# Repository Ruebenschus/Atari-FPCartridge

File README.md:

Atari-FPCartridge
=================

**Atari Field Programmable Cartridge**

Use an ULX3S FPGA to emulate an Atari ST cartridge.

Overview
--------

Atari-FPCartridge is a proof-of-concept adapter and FPGA design that connects a
ULX3S board to the Atari ST cartridge port. The goal is to make cartridge
development, boot analysis, ROM emulation, and hardware experimentation much
easier without building a custom FPGA board from scratch on day one.

The project combines:

-   a KiCad adapter PCB for the Atari ST cartridge connector and the ULX3S
    headers

-   level shifting between the 5 V Atari bus and the 3.3 V FPGA I/O

-   power-path selection between Atari 5 V and ULX3S USB 5 V

-   FPGA firmware for cartridge emulation, diagnostics, display output, and
    bus-oriented test modes

The result is a practical development platform for exploring what the Atari ST
expects at the cartridge port and for gradually moving toward more advanced
cartridge behavior.

Why ULX3S + FPGA
----------------

An FPGA is a good fit for this job because the Atari cartridge port is
fundamentally a parallel hardware interface. An FPGA can react
deterministically, observe many signals at once, and eventually emulate ROM
behavior with cycle-level control.

Compared with a Raspberry Pi or similar SBC:

-   **Advantages of the FPGA approach**

    -   deterministic timing

    -   direct parallel I/O handling

    -   much better fit for ROM emulation and bus experiments

    -   easier path toward cycle-precise cartridge behavior

-   **Disadvantages of the FPGA approach**

    -   HDL development is maybe more complex than software on Linux

    -   higher entry barrier for tooling and synthesis. I’m a hardware designer
        by trade, so it is my natural way of doing thing ;-)

    -   FPGAs are less common and potentially higher cost than e.g. RPI

-   **Advantages of an SBC approach**

    -   easier software stack

    -   networking, file systems, and UI are simpler

    -   fast prototyping for higher-level features

-   **Disadvantages of an SBC approach**

    -   GPIO timing is much less deterministic and has to be tweaked by RPI
        GPIOs

    -   parallel bus interfacing is harder

    -   extra hardware is usually needed to make the interface robust

The ULX3S offers a strong middle ground: a real FPGA, a convenient dev board,
USB programming, built-in buttons, LEDs, OLED support, HDMI video, and future
expansion options such as Wi-Fi-assisted workflows.

A note on SidecarTridge
-----------------------

This project is inspired by the excellent
[SidecarTridge](https://sidecartridge.com/) project. SidecarTridge shows how
much can be achieved when modern programmable logic and the Atari ST cartridge
port are combined thoughtfully. Atari-FPCartridge is not trying to diminish that
work. On the contrary, it is a respectful proof of concept built in the same
spirit: use todays hardware to tweak your old retro Atari and have fun as in the
golden days.  

Hardware
--------

### PCB scope

The adapter PCB is designed to sit between the Atari ST cartridge connector and
the ULX3S board. It provides:

-   Atari cartridge connector breakout

-   ULX3S header connections

-   bidirectional level shifters for the data bus

-   shifted input paths for address and control signals

-   power-path selection between USB power and Atari cartridge power

### Power

The board is intended to support powering the setup from either:

-   **ULX3S USB 5 V**

-   **Atari ST cartridge-port 5 V**

The power section is built around automatic source selection so that:

-   when USB power is present, the ULX3S can power itself and the level shifters
    locally

-   when USB power is absent, the adapter can be powered from the Atari
    cartridge port

This avoids a manual source switch in normal use and keeps the adapter much
easier to operate during development and bring-up.

### Signals

#### Unidirectional signals into the FPGA

These lines are treated as bus-observation inputs from the Atari side:

-   `A1..A15`

-   `ROM3#`

-   `ROM4#`

-   `UDS#`

-   `LDS#`

#### Bidirectional signals

These lines are routed through bidirectional level shifters:

-   `D0..D15`

They can be:

-   read by the FPGA during analysis and test modes

-   driven by the FPGA during cartridge emulation

-   driven selectively in debug output tests

#### FPGA-controlled transceiver signals

The level shifters expose separate control to the FPGA for:

-   `DIR4`

-   `OE4`

-   `DIR5`

-   `OE5`

That keeps the hardware flexible and allows different modes to switch between
safe sniffing, drive tests, and cartridge emulation behavior.

Repository structure
--------------------

-   `kicad/` - schematic, PCB, symbols, footprints

-   `stacy-cart-menu/` - FPGA design, constraints, ROM build flow

Operating modes
---------------

The FPGA project includes a menu on the OLED and several operating modes.

### `diag_cart`

This is the default power-up mode. It presents an Atari ST diagnostic cartridge
ROM image at the cartridge port so the machine can boot directly into the
diagnostic cartridge.

### `boot_analyzer`

This mode is intended to analyze the cartridge boot process and show how far the
system gets. It uses the OLED and the front-panel LEDs to indicate progress.

The LEDs are used as a step display:

-   a LED stays on when a step has been reached

-   a LED blinks slowly while the analyzer is waiting

-   a LED blinks quickly when a step times out or fails

This is useful for checking whether the expected cartridge accesses occur during
boot and whether the machine reaches the expected execution sequence.

### `beep`

This mode uses a small custom cartridge program that was created with AI
assistance and then integrated as a dedicated 68000-side test image. It
demonstrates that the FPGA can present a custom cartridge ROM and make the Atari
execute user-provided code.

In practical terms, it is a very small proof that the design can go beyond
passive observation and actively influence software execution through cartridge
ROM emulation. It makes the speaker beep to see whether the CPU is alive before
even accessing RAM or keyboard.

### `cart-debug`

The debug submenu contains low-level hardware test modes for board bring-up and
signal verification.  It is useful for pin verification and confirming that the
board routing matches the expected net mapping.

#### `drive`

This mode selects one signal at a time (selectable by buttons and OLED menu) and
toggles it at a visible rate so it can be checked with a multimeter or scope.
GP19 acts as read input any one can connect one output after another to the
input and see whether it is toggeling.

#### `read`

This mode is the opposite and lets the FPGA read external signal levels and show
them on the OLED. GP19 is enabled as 1Hz toggeling pin such that just with a
single cable on is capable of checking all solder connections and pins of the
board.  

OLED and LED diagnostics
------------------------

The OLED is used as the primary local UI. It shows:

-   the top-level menu

-   the currently selected cartridge mode

-   the current debug mode

-   analyzer state and captured addresses

The LEDs provide a quick visual status summary without needing to read the
display closely. This is especially useful while powering the Atari on, when
watching both the computer and the adapter at the same time.  
  
The Board also has a HDMI output which could be leveraged in future.  

Building and flashing
---------------------

~~~~~~~~~~~~~~~~~~~~~~~~~~~~~~~~~~~~~~~~~~~~~~~~~~~~~~~~~~~~~~~~~~~~~~~~~~~~~~~~
To build and program the FPGA design, the following tools are required:

- [oss-cad-suite](https://github.com/YosysHQ/oss-cad-suite-build) including:
  - `yosys`
  - `nextpnr-ecp5`
  - `ecppack`
  - `openFPGALoader`
- `python3`
- `make`

This project was developed with the ULX3S toolchain from `oss-cad-suite`.
~~~~~~~~~~~~~~~~~~~~~~~~~~~~~~~~~~~~~~~~~~~~~~~~~~~~~~~~~~~~~~~~~~~~~~~~~~~~~~~~

The FPGA project lives in `stacy-cart-menu/`.

### Build

~~~~~~~~~~~~~~~~~~~~~~~~~~~~~~~~~~~~~~~~~~~~~~~~~~~~~~~~~~~~~~~~~~~~~~~~~~~~~ sh
cd stacy-cart-menu
make build
~~~~~~~~~~~~~~~~~~~~~~~~~~~~~~~~~~~~~~~~~~~~~~~~~~~~~~~~~~~~~~~~~~~~~~~~~~~~~~~~

### Program SRAM

~~~~~~~~~~~~~~~~~~~~~~~~~~~~~~~~~~~~~~~~~~~~~~~~~~~~~~~~~~~~~~~~~~~~~~~~~~~~~ sh
make prog
~~~~~~~~~~~~~~~~~~~~~~~~~~~~~~~~~~~~~~~~~~~~~~~~~~~~~~~~~~~~~~~~~~~~~~~~~~~~~~~~

On some macOS setups, direct USB access to `openFPGALoader` may require `sudo`:

~~~~~~~~~~~~~~~~~~~~~~~~~~~~~~~~~~~~~~~~~~~~~~~~~~~~~~~~~~~~~~~~~~~~~~~~~~~~~ sh
sudo make prog
~~~~~~~~~~~~~~~~~~~~~~~~~~~~~~~~~~~~~~~~~~~~~~~~~~~~~~~~~~~~~~~~~~~~~~~~~~~~~~~~

### Flash configuration memory

~~~~~~~~~~~~~~~~~~~~~~~~~~~~~~~~~~~~~~~~~~~~~~~~~~~~~~~~~~~~~~~~~~~~~~~~~~~~~ sh
make flash
~~~~~~~~~~~~~~~~~~~~~~~~~~~~~~~~~~~~~~~~~~~~~~~~~~~~~~~~~~~~~~~~~~~~~~~~~~~~~~~~

If needed:

~~~~~~~~~~~~~~~~~~~~~~~~~~~~~~~~~~~~~~~~~~~~~~~~~~~~~~~~~~~~~~~~~~~~~~~~~~~~~ sh
sudo make flash
~~~~~~~~~~~~~~~~~~~~~~~~~~~~~~~~~~~~~~~~~~~~~~~~~~~~~~~~~~~~~~~~~~~~~~~~~~~~~~~~

### Detect the board

~~~~~~~~~~~~~~~~~~~~~~~~~~~~~~~~~~~~~~~~~~~~~~~~~~~~~~~~~~~~~~~~~~~~~~~~~~~~~ sh
make detect
~~~~~~~~~~~~~~~~~~~~~~~~~~~~~~~~~~~~~~~~~~~~~~~~~~~~~~~~~~~~~~~~~~~~~~~~~~~~~~~~

or:

~~~~~~~~~~~~~~~~~~~~~~~~~~~~~~~~~~~~~~~~~~~~~~~~~~~~~~~~~~~~~~~~~~~~~~~~~~~~~ sh
sudo make detect
~~~~~~~~~~~~~~~~~~~~~~~~~~~~~~~~~~~~~~~~~~~~~~~~~~~~~~~~~~~~~~~~~~~~~~~~~~~~~~~~

<br>ROM content
---------------

The current setup demonstrates two distinct cartridge content styles:

-   a real diagnostic cartridge ROM image

-   a small custom cartridge program for the beep mode

The beep cartridge is particularly important because it proves that this
platform is not limited to replaying an existing ROM dump. It can also expose
newly created cartridge software and use that to control the Atari from the
cartridge side.

<br>What this enables
---------------------

Even in its current proof-of-concept form, the project already points toward a
much larger set of possibilities:

-   loading arbitrary cartridge images into FPGA-backed ROM

-   testing new custom Atari ST cartridge software

-   observing cartridge-port activity during boot and diagnostics

-   building more advanced debug and development tools

-   using the ULX3S platform as a fast iteration environment before designing a
    dedicated board

With more work, this platform could also grow toward network-assisted workflows
using the ULX3S ecosystem, including Wi-Fi-enabled cartridge management and
other higher-level features in the spirit of
[SidecarTridge](https://sidecartridge.com/). More broadly, it suggests a path
toward many of the capabilities demonstrated by SidecarTridge, while staying
focused here on a compact and understandable FPGA-first proof of concept.

<br>Outlook
-----------

This project is intentionally a proof of concept. The current adapter uses a
full ULX3S development board because that makes experimentation fast and
practical.

If there is enough interest, the next logical step would be a much smaller
dedicated cartridge board that integrates only:

-   the FPGA

-   the level shifters

-   the power-path logic

-   the cartridge interface

That would reduce size, cost, and assembly complexity while preserving the
lessons learned from this development platform.

But guys, imagine how blown away I was when my STacy first bootet from a debug
cartridge I loaded into “my” FPGA and that it was possible to ask AI to
“generate a 68000 binary that beeps the speaker” is actually working 🤩🤩🤩 You
can use this to create your own code and load it on your Atari.  

It can also be used to actively readout real cartridges and store their content on the FPGA and readout over USB...

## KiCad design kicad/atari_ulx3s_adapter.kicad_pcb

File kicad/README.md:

# KiCAD-Projekt-Ordner

## Was hier liegt

| Datei | Zweck |
|-------|-------|
| `atari_ulx3s_adapter.kicad_pro` | Projektfile, mit KiCAD 8+ öffnen |
| `atari_ulx3s_adapter.kicad_sch` | Schematic-Startversion (8 Komponenten platziert, keine Drähte) |
| `atari_ulx3s.kicad_sym` | Custom Symbol Library (4 Symbole, verifiziert) |
| `sym-lib-table` | Library-Tabelle, damit KiCAD die Custom-Lib findet |

## So öffnest du das Projekt

1. **KiCAD 8 oder neuer** starten
2. Project File öffnen: `atari_ulx3s_adapter.kicad_pro`
3. KiCAD wird die Custom-Library aus `sym-lib-table` automatisch laden
4. Schematic Editor öffnen (Doppelklick auf Schematic-Eintrag oder F1)

## Was du im Schematic siehst

8 Komponenten in 3 Spalten platziert:

- **Links:** Atari Cart Edge Connector (J1) — 40-pin Edge-Connector
- **Mitte:** 5× 74LVC4245A (U1–U5) übereinander
- **Rechts:** ULX3S J1 Socket (J2) oben, ULX3S J2 Socket (J3) unten

Keine Drähte — du zeichnest die Verbindungen nach `03_netlist_connections.md`.

## Was du noch hinzufügen musst (aus KiCAD-Standard-Libs)

Diese Komponenten habe ich NICHT in der Custom-Lib generiert, weil sie aus KiCAD-Standard-Bibliotheken kommen (Device, Switch, Connector_Generic, power):

- **R1, R2** — 10 kΩ Pullup nach +5V_BUS (für DOE_N und DIR_D)
- **R3, R4** — 1 kΩ Vorwiderstände für Status-LEDs
- **C1** — 10 µF Tantal Bulk (5V-Schiene)
- **C2** — 10 µF (3.3V-Schiene)
- **C3–C12** — 100 nF Decoupling (2 pro Shifter, je 1× VCCA + 1× VCCB)
- **D1, D2** — LED grün/rot für USB/Atari Power-Indikator
- **SW1** — SPDT Slide-Switch (z.B. `Switch:SW_SPDT`)
- **TP1–TP5** — Test-Points für U3 Reserve-Pins
- **Power-Flags** — `+5V`, `+3V3`, `GND` (aus `power` Library)
- **Power-Nets** (Custom-Labels):
  - `+5V_BUS` (nach SW1 Common)
  - `+5V_USB` (zwischen ULX3S J2-5V-Pin und SW1)
  - `+5V_ATARI` (zwischen Atari Cart Pin 1+2 und SW1)

## Verdrahtungs-Recipe

Folge der Tabelle in `../03_netlist_connections.md`. Für jeden Atari-Pin:

1. Setze einen Wire vom Cart-Pin (links) auf einen 74LVC4245A-A-Pin (Mitte)
2. Vom B-Pin (3.3V-Seite) auf den ULX3S-Header-Pin (rechts)
3. Beide Wire-Endpunkte können auch ein Net-Label bekommen — KiCAD verbindet alles mit gleichem Label

Alternativ (schneller): mit `Add Label` einen Net-Namen auf jeden Pin packen.
Z.B. an Cart-Pin 36 (A1) Label "A1", an U1-Pin 3 (A1-Eingang) auch "A1" — KiCAD
verbindet die beiden ohne Wire-Routing.

## Power-Anschlüsse (Beispiel-Wires)

```
Cart J1 Pin 1   ── +5V_ATARI ──┐
Cart J1 Pin 2   ── +5V_ATARI ──┴── SW1 Pin 2

ULX3S J2 Pin 1  ── +5V_USB ────┐
ULX3S J2 Pin 2  ── +5V_USB ────┴── SW1 Pin 1

SW1 Pin 3       ── +5V_BUS ────┬── U1 VCCA (Pin 1)
                                ├── U2 VCCA
                                ├── U3 VCCA
                                ├── U4 VCCA
                                ├── U5 VCCA
                                ├── R1 (Pullup DOE_N)
                                ├── R2 (Pullup DIR_D)
                                └── ULX3S J2 Pin 1 (zurück, mit Schottky D1)

ULX3S J1 Pin 1  ── +3V3 ───────┬── U1 VCCB (Pin 23, 24)
                                ├── U2..U5 VCCB
                                └── Decoupling Caps

GND             ── globaler Net, alle GNDs verbinden
```

## ERC-Tipps

Nach dem Verdrahten:
1. **Inspect → Run Electrical Rules Checker (ERC)** ausführen
2. Häufige Warnings:
   - "Pin not connected" auf den NC- oder Reserve-Pins → bei TP1–TP5 absichtlich; Markieren mit "Add no-connect flag"
   - "Power input not driven" → Power-Flag fehlt; ein `(power)` Symbol pro Power-Net hinzufügen
3. Fehler **dürfen nicht** vorhanden sein — wenn doch, im Pinout (Doc 03) gegenchecken

## Beim Übergang zu PCB-Layout (Phase 5)

1. Im Schematic: **Tools → Update PCB from Schematic** (F8)
2. Dabei werden die Footprints aus den `Footprint`-Properties geladen:
   - `Package_SO:SSOP-24_5.3x8.2mm_P0.65mm` für 74LVC4245A
   - `Connector_PinSocket_2.54mm:PinSocket_2x20_P2.54mm_Vertical` für ULX3S-Header
   - `atari_ulx3s_adapter:CartEdge_40Pin_ST` — den müssen wir noch erzeugen (Custom Footprint für den Atari-Edge-Connector)
3. Pull-/Cap-/LED-/Switch-Footprints werden automatisch aus den KiCAD-Standard-Footprint-Libs gezogen

## Bei Fragen

Schau in die Phase-Docs im Parent-Ordner:
- `01_pinout_signal_analyse.md` — Signal-Bedeutung
- `02_levelshifter_und_power.md` — Power-Strategie + Switch
- `03_netlist_connections.md` — exakte Net-Liste (das Master-Doc für Verdrahtung)
- `04_pin_verification_findings.md` — was bei Verifikation gefixt wurde
- `Doku/ulx3s_J1_J2_pinout.md` — physische ULX3S-Pin-Belegung

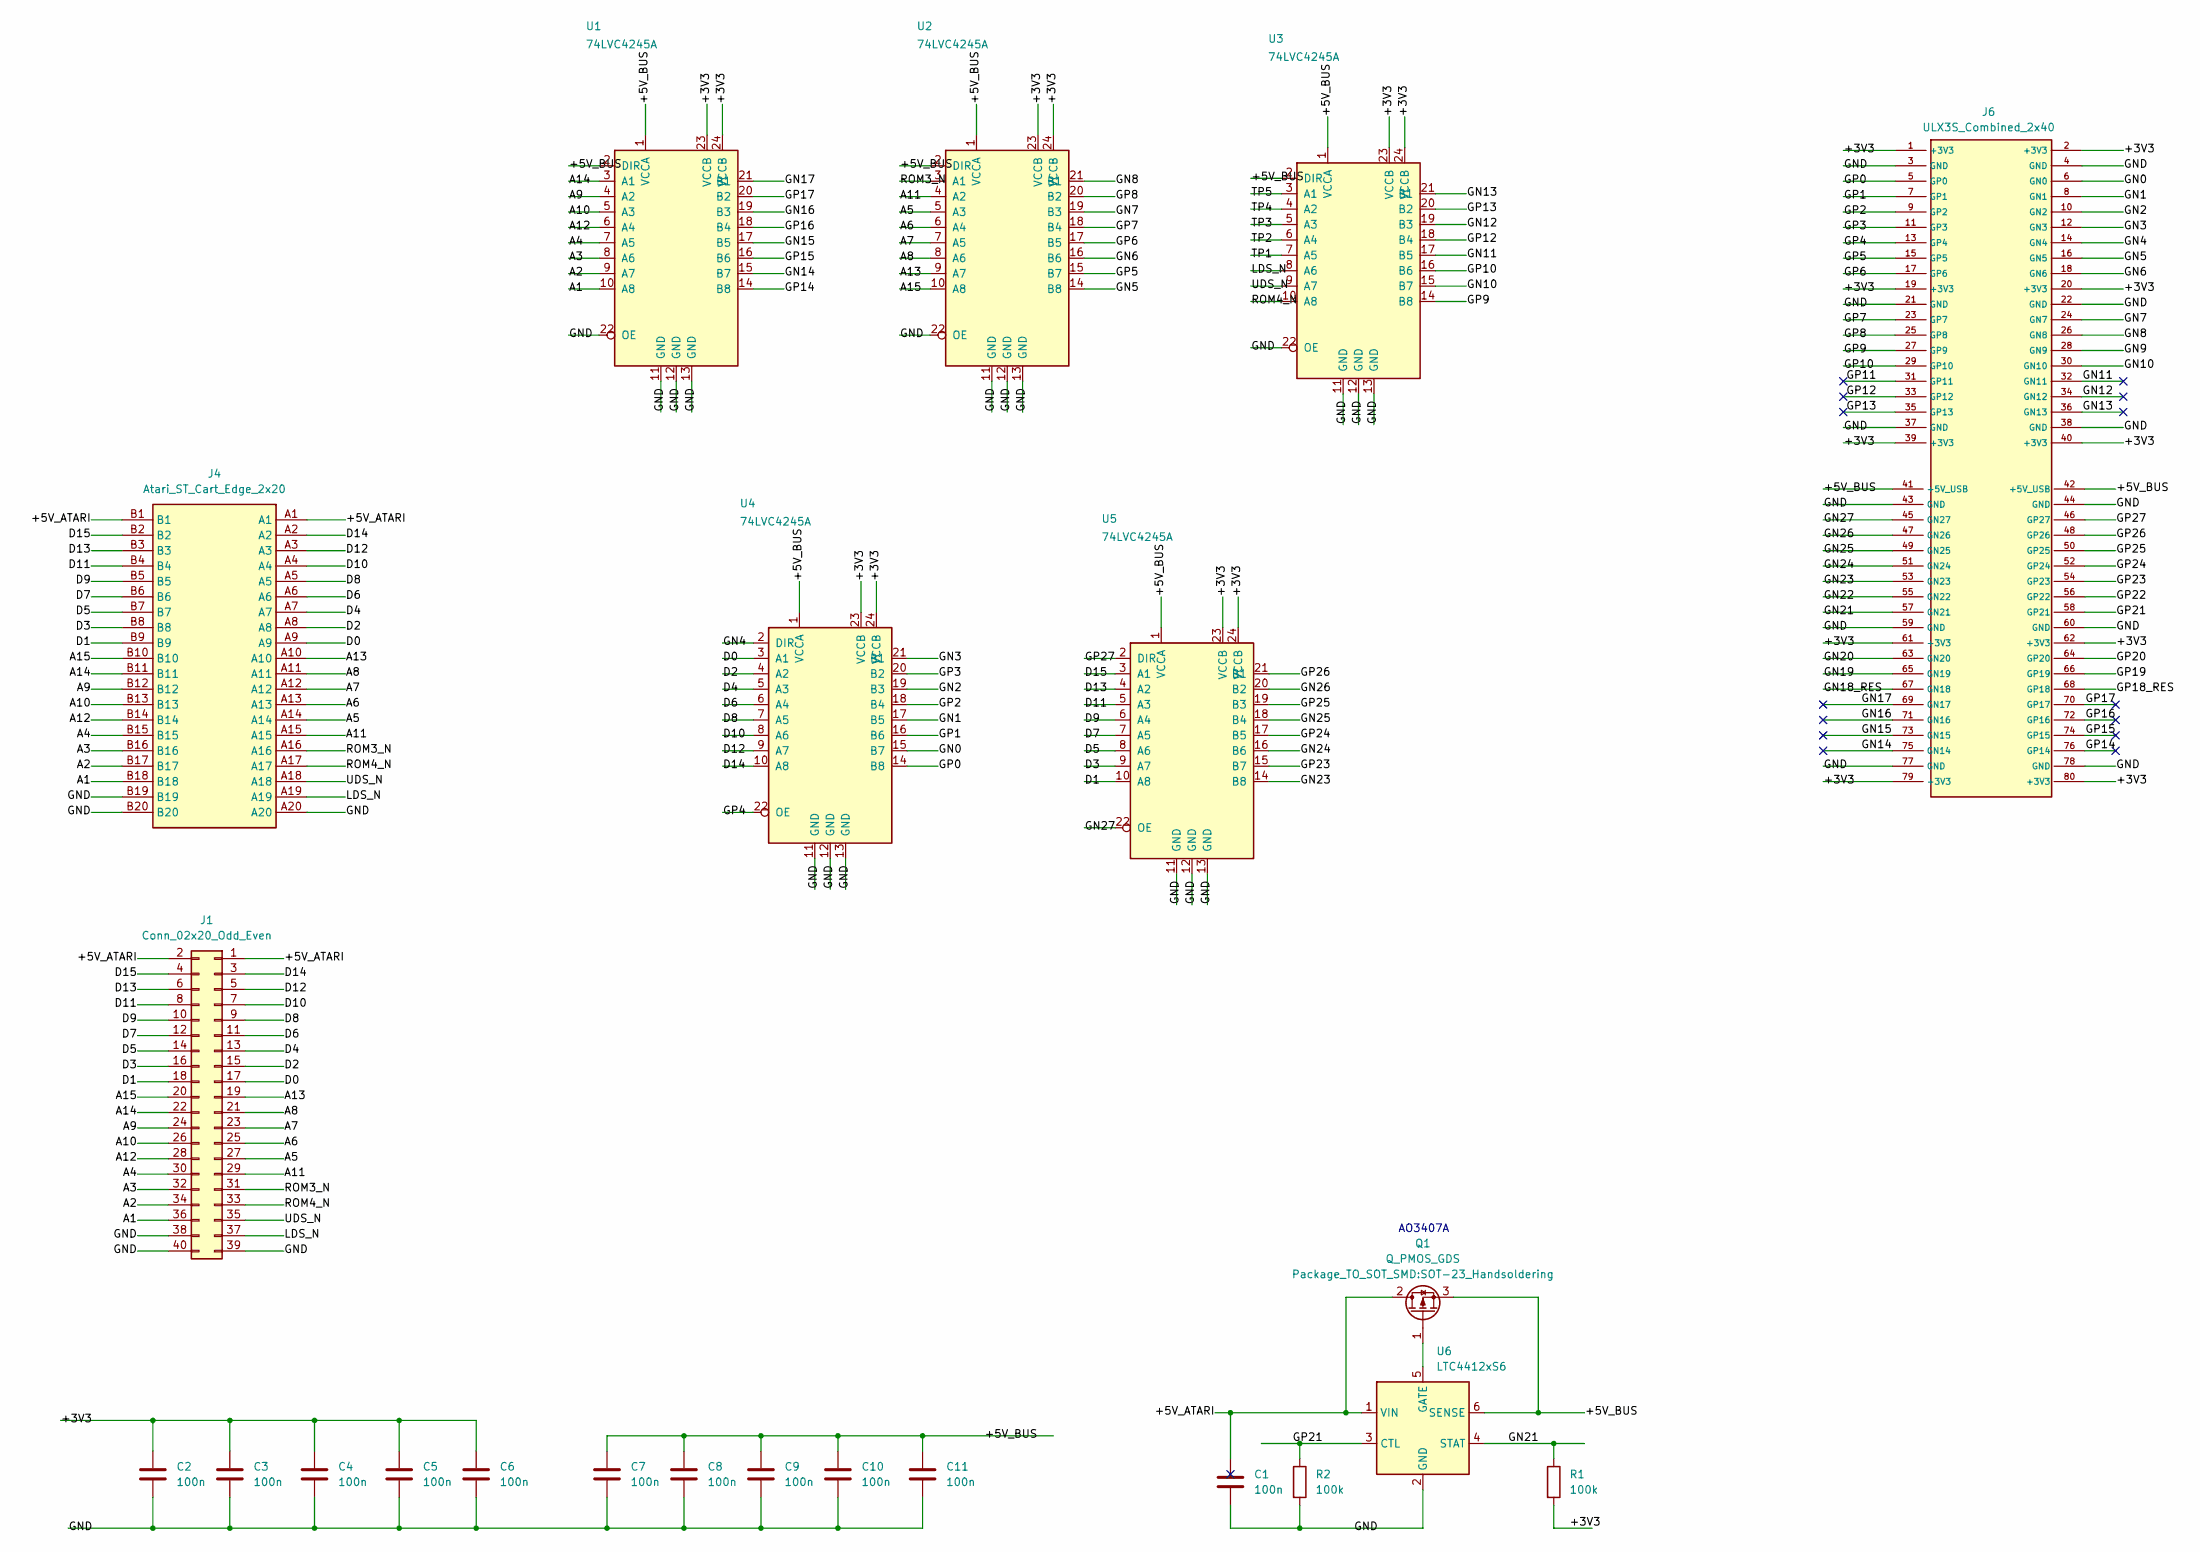
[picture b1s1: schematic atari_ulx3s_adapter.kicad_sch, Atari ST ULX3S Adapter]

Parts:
C1, C2, C3, C4, C5, C6, C7, C8, C9, C10, C11: 100n; C_0805_2012Metric_Pad1.18x1.45mm_HandSolder
J1: Conn_02x20_Odd_Even; PinHeader_2x20_P2.54mm_Vertical
J4: Atari_ST_Cart_Edge_2x20; Atari_ST_Cartridge_Edge_2x20_P2.00mm
J6: ULX3S_Combined_2x40; ULX3S_Module
Q1: Q_PMOS_GDS; SOT-23_Handsoldering
R1, R2: 100k; R_0805_2012Metric_Pad1.20x1.40mm_HandSolder
U1, U2, U3, U4, U5: 74LVC4245A; SOIC-24W_7.5x15.4mm_P1.27mm
U6: LTC4412xS6; TSOT-23-6

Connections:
/+3V3: C2.1, C3.1, C4.1, C5.1, C6.1, J6.1 (+3V3), J6.2 (+3V3), J6.19 (+3V3), J6.20 (+3V3), J6.39 (+3V3), J6.40 (+3V3), J6.61 (+3V3), J6.62 (+3V3), J6.79 (+3V3), J6.80 (+3V3), R1.2, U1.23 (VCCB), U1.24 (VCCB), U2.23 (VCCB), U2.24 (VCCB), U3.23 (VCCB), U3.24 (VCCB), U4.23 (VCCB), U4.24 (VCCB), U5.23 (VCCB), U5.24 (VCCB)
/+5V_ATARI: C1.1, J1.1, J1.2, J4.A1, J4.B1, Q1.2 (D), U6.1 (VIN)
/+5V_BUS: C7.1, C8.1, C9.1, C10.1, C11.1, J6.41 (+5V_USB), J6.42 (+5V_USB), Q1.3 (S), U1.1 (VCCA), U1.2 (DIR), U2.1 (VCCA), U2.2 (DIR), U3.1 (VCCA), U3.2 (DIR), U4.1 (VCCA), U5.1 (VCCA), U6.6 (SENSE)
/A1: J1.36, J4.B18, U1.10 (A8)
/A2: J1.34, J4.B17, U1.9 (A7)
/A3: J1.32, J4.B16, U1.8 (A6)
/A4: J1.30, J4.B15, U1.7 (A5)
/A5: J1.27, J4.A14, U2.5 (A3)
/A6: J1.25, J4.A13, U2.6 (A4)
/A7: J1.23, J4.A12, U2.7 (A5)
/A8: J1.21, J4.A11, U2.8 (A6)
/A9: J1.24, J4.B12, U1.4 (A2)
/A10: J1.26, J4.B13, U1.5 (A3)
/A11: J1.29, J4.A15, U2.4 (A2)
/A12: J1.28, J4.B14, U1.6 (A4)
/A13: J1.19, J4.A10, U2.9 (A7)
/A14: J1.22, J4.B11, U1.3 (A1)
/A15: J1.20, J4.B10, U2.10 (A8)
/D0: J1.17, J4.A9, U4.3 (A1)
/D1: J1.18, J4.B9, U5.10 (A8)
/D2: J1.15, J4.A8, U4.4 (A2)
/D3: J1.16, J4.B8, U5.9 (A7)
/D4: J1.13, J4.A7, U4.5 (A3)
/D5: J1.14, J4.B7, U5.8 (A6)
/D6: J1.11, J4.A6, U4.6 (A4)
/D7: J1.12, J4.B6, U5.7 (A5)
/D8: J1.9, J4.A5, U4.7 (A5)
/D9: J1.10, J4.B5, U5.6 (A4)
/D10: J1.7, J4.A4, U4.8 (A6)
/D11: J1.8, J4.B4, U5.5 (A3)
/D12: J1.5, J4.A3, U4.9 (A7)
/D13: J1.6, J4.B3, U5.4 (A2)
/D14: J1.3, J4.A2, U4.10 (A8)
/D15: J1.4, J4.B2, U5.3 (A1)
/GN0: J6.6 (GN0), U4.15 (B7)
/GN1: J6.8 (GN1), U4.17 (B5)
/GN2: J6.10 (GN2), U4.19 (B3)
/GN3: J6.12 (GN3), U4.21 (B1)
/GN4: J6.14 (GN4), U4.2 (DIR)
/GN5: J6.16 (GN5), U2.14 (B8)
/GN6: J6.18 (GN6), U2.16 (B6)
/GN7: J6.24 (GN7), U2.19 (B3)
/GN8: J6.26 (GN8), U2.21 (B1)
/GN9: J6.28 (GN9)
/GN10: J6.30 (GN10), U3.15 (B7)
/GN11: J6.32 (GN11), U3.17 (B5)
/GN12: J6.34 (GN12), U3.19 (B3)
/GN13: J6.36 (GN13), U3.21 (B1)
/GN14: J6.75 (GN14), U1.15 (B7)
/GN15: J6.73 (GN15), U1.17 (B5)
/GN16: J6.71 (GN16), U1.19 (B3)
/GN17: J6.69 (GN17), U1.21 (B1)
/GN18_RES: J6.67 (GN18)
/GN19: J6.65 (GN19)
/GN20: J6.63 (GN20)
/GN21: J6.57 (GN21), R1.1, U6.4 (STAT)
/GN22: J6.55 (GN22)
/GN23: J6.53 (GN23), U5.14 (B8)
/GN24: J6.51 (GN24), U5.16 (B6)
/GN25: J6.49 (GN25), U5.18 (B4)
/GN26: J6.47 (GN26), U5.20 (B2)
/GN27: J6.45 (GN27), U5.22 (OE)
/GND: C1.2, C2.2, C3.2, C4.2, C5.2, C6.2, C7.2, C8.2, C9.2, C10.2, C11.2, J1.38, J1.39, J1.40, J4.A20, J4.B19, J4.B20, J6.3 (GND), J6.4 (GND), J6.21 (GND), J6.22 (GND), J6.37 (GND), J6.38 (GND), J6.43 (GND), J6.44 (GND), J6.59 (GND), J6.60 (GND), J6.77 (GND), J6.78 (GND), R2.2, U1.11 (GND), U1.12 (GND), U1.13 (GND), U1.22 (OE), U2.11 (GND), U2.12 (GND), U2.13 (GND), U2.22 (OE), U3.11 (GND), U3.12 (GND), U3.13 (GND), U3.22 (OE), U4.11 (GND), U4.12 (GND), U4.13 (GND), U5.11 (GND), U5.12 (GND), U5.13 (GND), U6.2 (GND)
/GP0: J6.5 (GP0), U4.14 (B8)
/GP1: J6.7 (GP1), U4.16 (B6)
/GP2: J6.9 (GP2), U4.18 (B4)
/GP3: J6.11 (GP3), U4.20 (B2)
/GP4: J6.13 (GP4), U4.22 (OE)
/GP5: J6.15 (GP5), U2.15 (B7)
/GP6: J6.17 (GP6), U2.17 (B5)
/GP7: J6.23 (GP7), U2.18 (B4)
/GP8: J6.25 (GP8), U2.20 (B2)
/GP9: J6.27 (GP9), U3.14 (B8)
/GP10: J6.29 (GP10), U3.16 (B6)
/GP11: J6.31 (GP11)
/GP12: J6.33 (GP12), U3.18 (B4)
/GP13: J6.35 (GP13), U3.20 (B2)
/GP14: J6.76 (GP14), U1.14 (B8)
/GP15: J6.74 (GP15), U1.16 (B6)
/GP16: J6.72 (GP16), U1.18 (B4)
/GP17: J6.70 (GP17), U1.20 (B2)
/GP18_RES: J6.68 (GP18)
/GP19: J6.66 (GP19)
/GP20: J6.64 (GP20)
/GP21: J6.58 (GP21), R2.1, U6.3 (CTL)
/GP22: J6.56 (GP22)
/GP23: J6.54 (GP23), U5.15 (B7)
/GP24: J6.52 (GP24), U5.17 (B5)
/GP25: J6.50 (GP25), U5.19 (B3)
/GP26: J6.48 (GP26), U5.21 (B1)
/GP27: J6.46 (GP27), U5.2 (DIR)
/LDS_N: J1.37, J4.A19, U3.8 (A6)
/ROM3_N: J1.31, J4.A16, U2.3 (A1)
/ROM4_N: J1.33, J4.A17, U3.10 (A8)
/TP1: U3.7 (A5)
/TP2: U3.6 (A4)
/TP3: U3.5 (A3)
/TP4: U3.4 (A2)
/TP5: U3.3 (A1)
/UDS_N: J1.35, J4.A18, U3.9 (A7)
unnamed: Q1.1 (G), U6.5 (GATE)

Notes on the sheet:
AO3407A

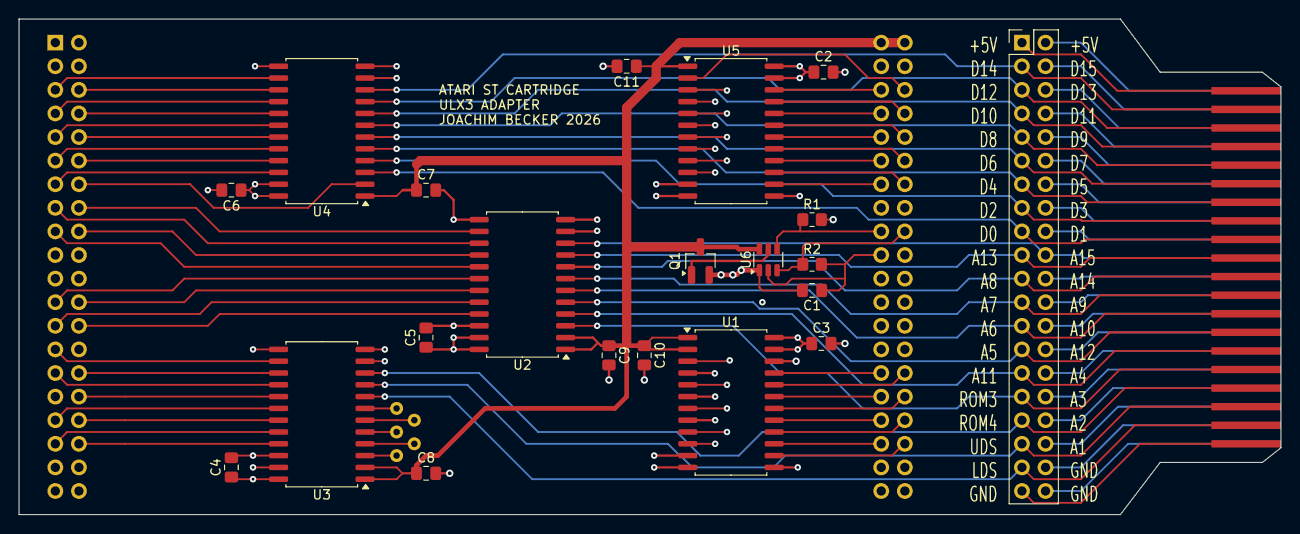
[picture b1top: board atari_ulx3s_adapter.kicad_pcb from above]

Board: 4 copper layers, 135.8 x 53.3 mm, 23 parts (0 on the bottom side), 86 nets.
